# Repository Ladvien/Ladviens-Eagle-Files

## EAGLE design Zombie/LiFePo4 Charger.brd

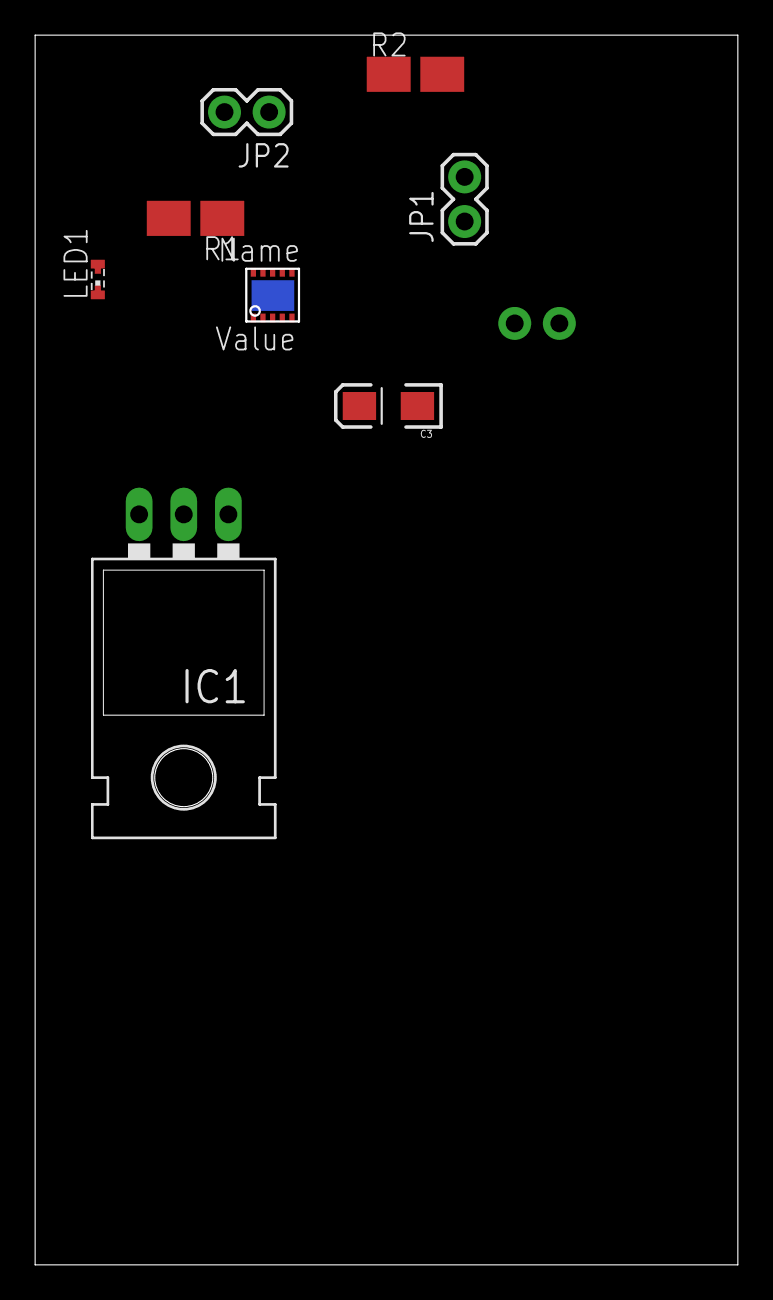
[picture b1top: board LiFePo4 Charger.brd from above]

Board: 2 copper layers, 40.0 x 70.0 mm, 9 parts (1 on the bottom side), 8 nets, no tracks yet.

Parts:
C3: 4.7; EIA3216-KIT
IC1: 5v; TO-220-ALT
JP1: Bat+; 1X02
JP2: Bat-; 1X02
JP3: Vraw/Grnd; 1X02
LED1: 250mcd; SMARTLED-TTW
R1: 1.5k; SMK
R2: 1k; SMK
U$8: MCP73123/223

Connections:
GND: C3.C, IC1.GND, JP3.1
unnamed: IC1.IN, JP3.2
unnamed: C3.A, IC1.OUT, LED1.A@1, U$8.1, U$8.2
unnamed: JP1.1, JP1.2, U$8.3, U$8.4
unnamed: R1.1, U$8.10
unnamed: JP2.1, JP2.2, R1.2, U$8.8, U$8.9
unnamed: LED1.C@1, R2.2
unnamed: R2.1, U$8.7

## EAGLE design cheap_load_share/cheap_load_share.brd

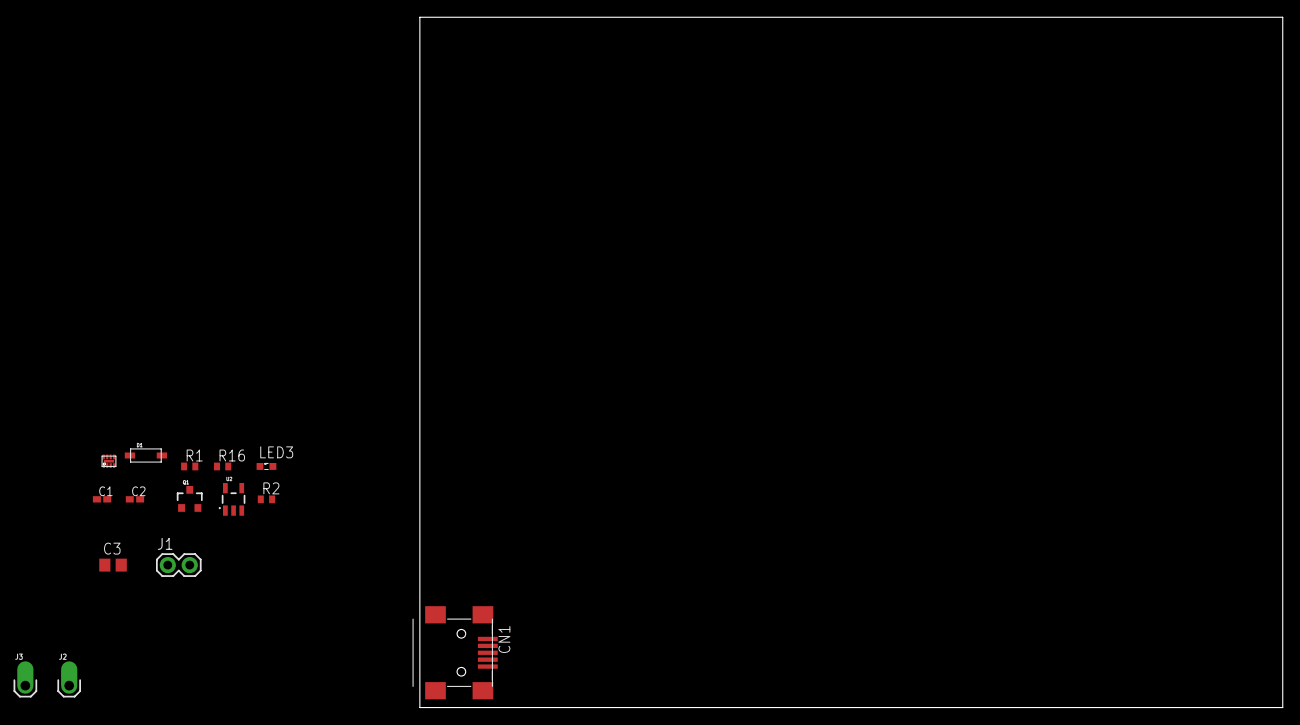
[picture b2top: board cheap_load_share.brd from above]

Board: 2 copper layers, 136.7 x 80.0 mm, 15 parts (0 on the bottom side), 8 nets, no tracks yet.

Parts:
C1: 1uF; C0402K
C2: 4.7uF; C0402K
C3: 4.7uF; C0805
CN1: USB-MINIB
D1: B130LAW; SOD-123
J1: 3.7_LIPO; 1X02
J2, J3: 1X01_OFFSET
LED3: SML0603
Q1: DMP1045U; SOT23-3
R1, R16: R0402
R2: 100K; R0402
U2: MCP73831; SOT23-5
U$4: NCP186-AMX; XDFN8

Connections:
5V: C2.1, CN1.VBUS, D1.A, Q1.1, R2.2, R16.2, U2.4
GND: C1.2, C2.2, C3.2, CN1.GND, CN1.GND1, CN1.GND2, CN1.GND3, CN1.GND4, J1.2, J3.1, R1.1, R2.1, U2.2, U$4.5, U$4.PAD
unnamed: LED3.A, R16.1
unnamed: LED3.C, U2.1
unnamed: R1.2, U2.5
V+: C1.1, D1.C, J2.1, Q1.2, U$4.6, U$4.7, U$4.8
VCC: U$4.1, U$4.2, U$4.4
V_BATT: C3.1, J1.1, Q1.3, U2.3

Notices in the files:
parts and their libraries:
SparkFun: Licensing: CC v3.0 Share-Alike You are welcome to use this library for commercial purposes.
SparkFun-Connectors: Licensing: Creative Commons ShareAlike 4.0 International - https://creativecommons.org/licenses/by-sa/4.0
